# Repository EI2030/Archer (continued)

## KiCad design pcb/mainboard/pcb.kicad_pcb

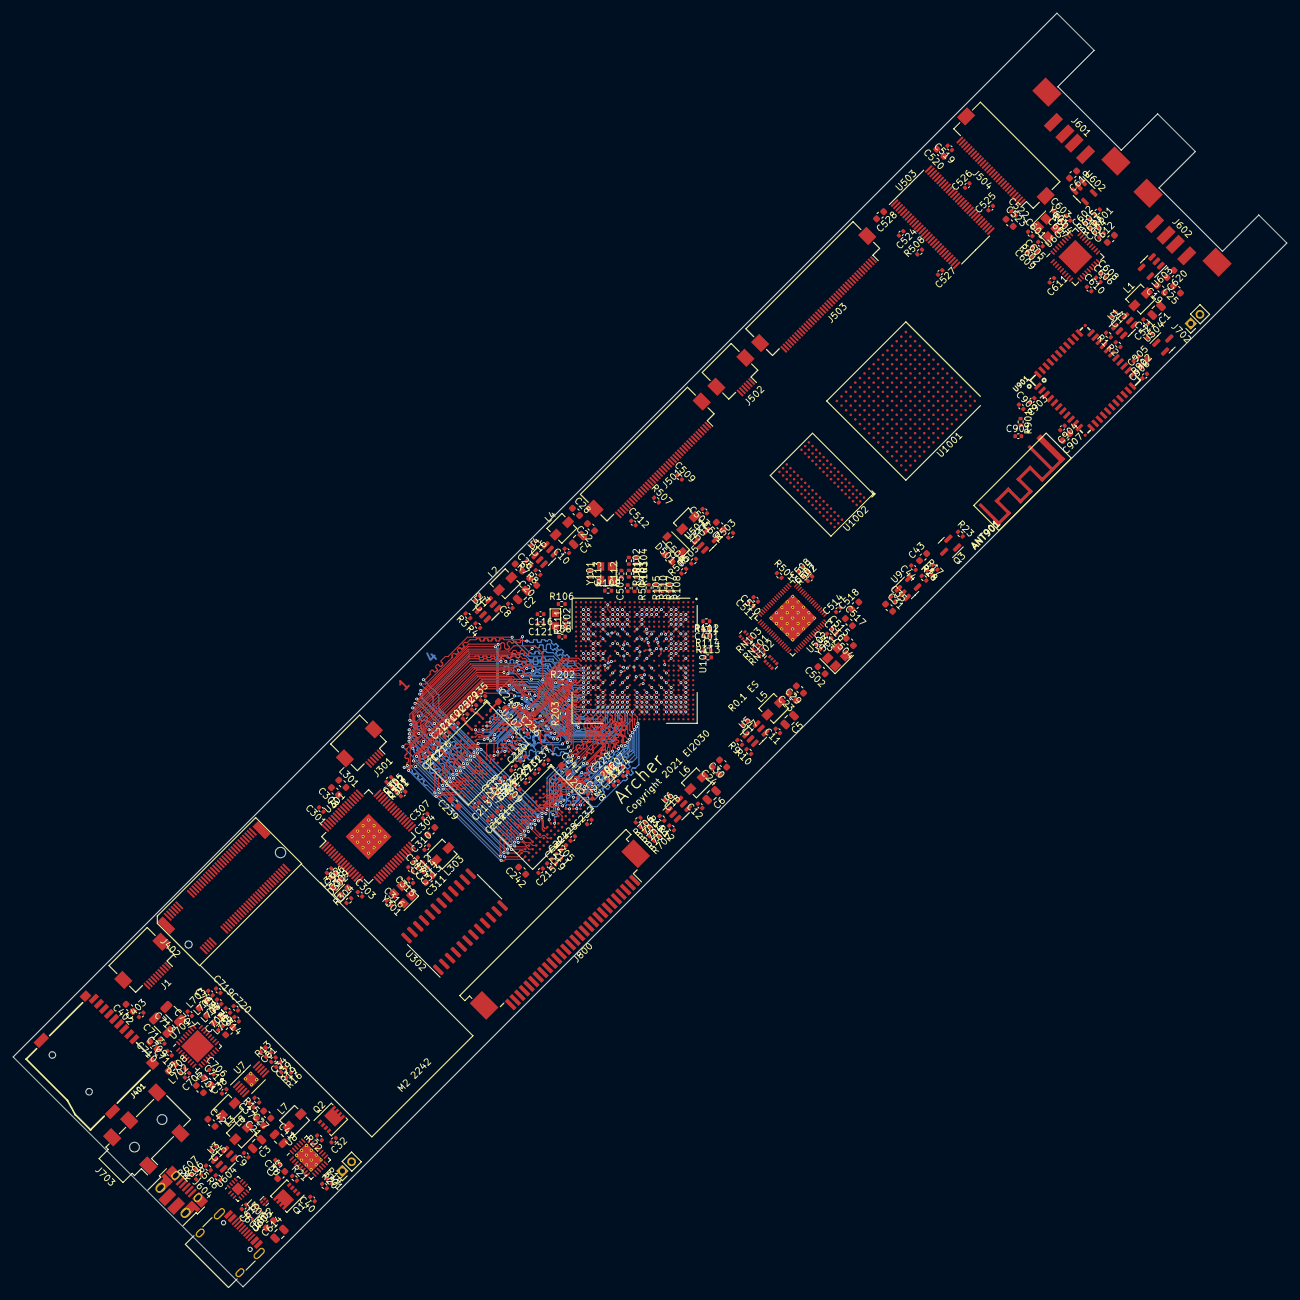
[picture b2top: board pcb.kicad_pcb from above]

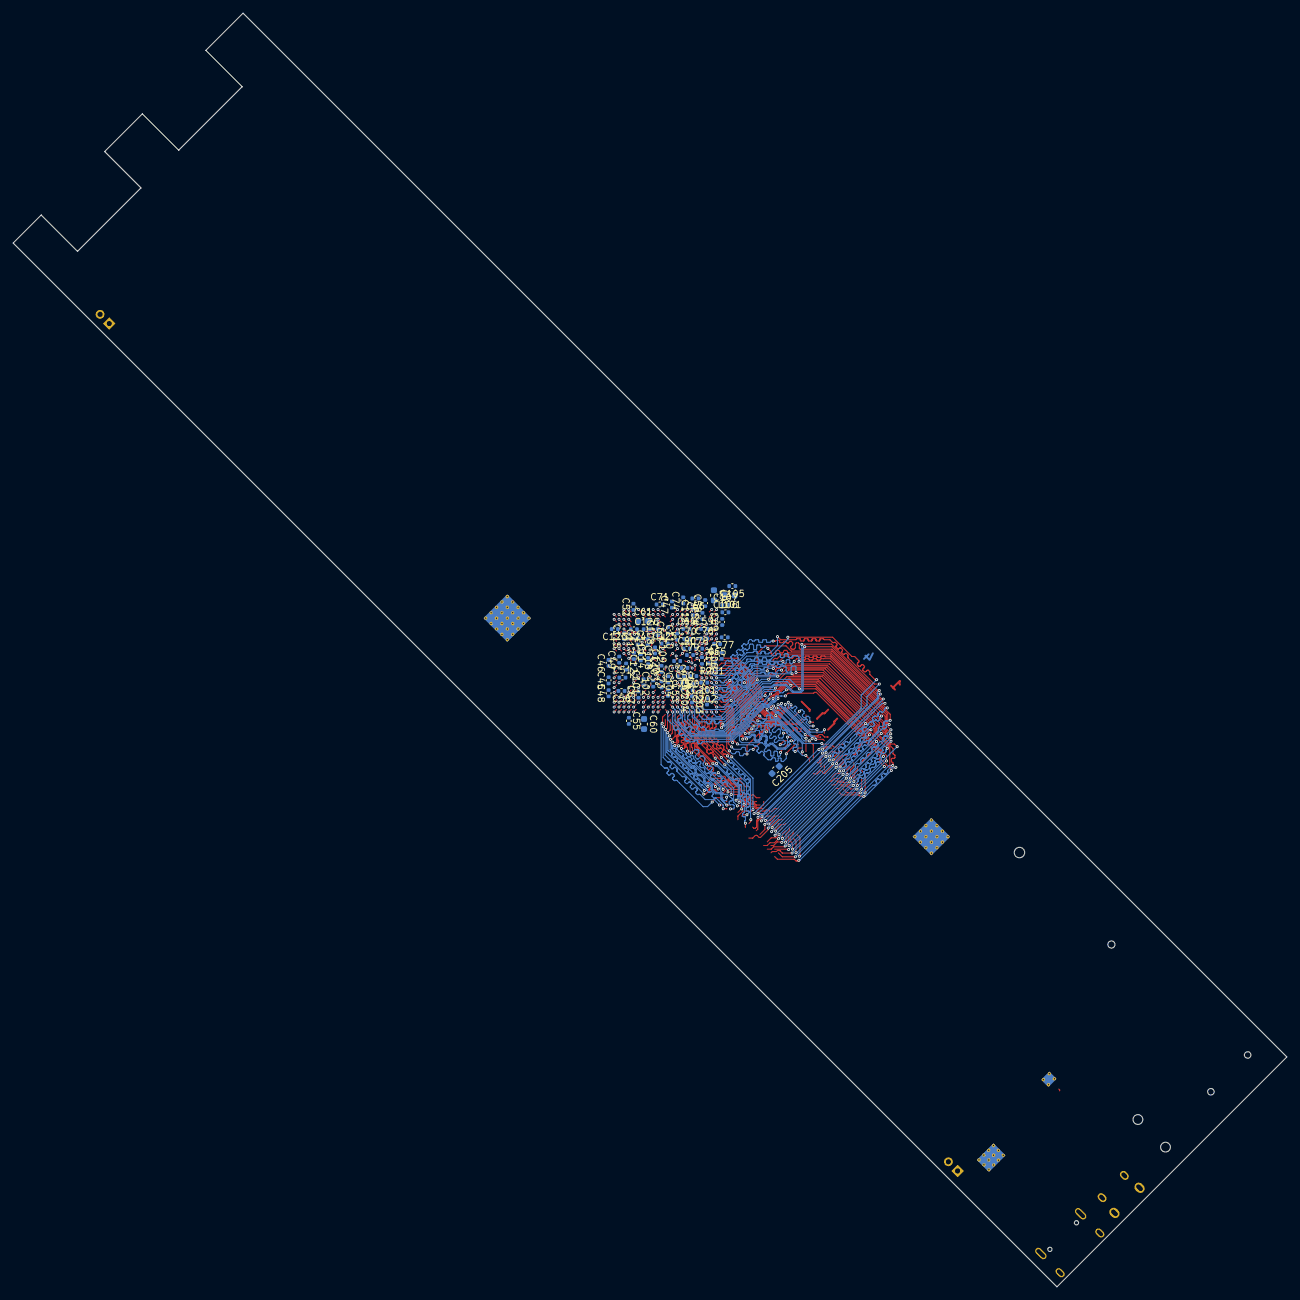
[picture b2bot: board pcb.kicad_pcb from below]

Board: 4 copper layers, 195.9 x 195.9 mm, 388 parts (68 on the bottom side), 385 nets.

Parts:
ANT901: PCB_WIFI_ANT; bt_antenna_1ant_2gnd
C1, C2, C3, C4, C5, C6: 4.7uF/25V; C_0805_2012Metric
C7, C8, C9, C10, C11, C12, C13, C14, C15, C16, C17, C18, C35, C37, C38, C40, C44, C206, C233, C234, C301, C302, C303, C305, C306, C307, C313, C317, C403, C503, C509, C512, C519, C521, C522, C602, C604, C605, C606, C607, C608, C609, C610, C611, C613, C714, C715, C716, C717, C718, C904, C906: 100nF; C_0402_1005Metric
C19, C20, C21, C22, C23, C24, C25, C26, C27, C28, C29, C30, C31, C42, C308, C501, C905, C907: 10uF; C_0603_1608Metric
C32, C81: 1uF; C_0402_1005Metric
C33, C43, C220, C710, C711: 4.7uF; C_0603_1608Metric
C34: 10nF; C_0402_1005Metric
C36: 22nF; C_0402_1005Metric
C39: 10pF; C_0402_1005Metric
C41, C614: 10uF/25V; C_0805_2012Metric
C45, C46, C47, C48, C49, C50, C51, C52, C53, C54, C55, C56, C57, C59, C62, C63, C64, C65, C66, C67, C71, C72, C73, C74, C75, C76, C78, C79, C101, C102, C103, C105, C106, C108, C109, C111, C114, C115, C117, C118, C122, C123, C124, C125, C201, C202, C203, C204, C207, C208, C209, C210, C211, C212, C213, C214, C215, C216, C217, C218, C219, C221, C222, C223, C224, C225, C226, C227, C228, C229, C230, C231, C232, C235, C236, C237, C238, C505, C507, C508, C510, C511, C513, C514, C515, C516, C524, C525, C526, C527: 220nF; C_0402_1005Metric
C58, C68, C69, C70, C77, C80, C104, C107, C110, C119, C120, C126, C309, C314: 2.2uF; C_0402_1005Metric
C60, C61, C205, C239, C240, C241, C242, C304, C311, C402, C517, C518, C528: 22uF; C_0603_1608Metric
C112, C113, C315, C316, C401, C601, C603: 18pF; C_0402_1005Metric
C116, C121: DNP/18pF; C_0402_1005Metric
C310, C312: 47pF; C_0402_1005Metric
C502, C504: 18pF; C_0603_1608Metric
C506: 1uF/35V; C_0603_1608Metric
C520, C523, C612, C619, C620: 10uF/6.3V; C_0603_1608Metric
C705, C706, C707, C708, C709, C719, C720: 470nF; C_0402_1005Metric
C712, C713: 100uF; C_1206_3216Metric
C901, C902: DNP; C_0402_1005Metric
C903: 33pF/50V/5%; C_0402_1005Metric
D302: LED; LED_0603_1608Metric
D501: MBR0530; D_SOD-123
J1: Conn_01x10_MountingPin; Hirose_FH12-10S-0.5SH_1x10-1MP_P0.50mm_Horizontal
J301, J502: Conn_01x06_MountingPin; Hirose_FH12-6S-0.5SH_1x06-1MP_P0.50mm_Horizontal
J401: MICRO_SD(TFC-WPAPR-08); TFC-WPAPR-08
J402: Bus_M.2_Socket_B; M2_BKEY
J501, J503: Conn_01x40_MountingPin; Hirose_FH12-40S-0.5SH_1x40-1MP_P0.50mm_Horizontal
J504: Conn_01x28_MountingPin; Hirose_FH12-28S-0.5SH_1x28-1MP_P0.50mm_Horizontal
J601, J602: USB_A; Connector_USB_905-562A2021S10100
J603: USB_C_Receptacle_USB2.0; USB_C_Receptacle_HRO_TYPE-C-31-M-12
J604: USB_B_Micro; USB_Micro-B_Amphenol_10103594-0001LF_Horizontal
J701, J702: Conn_01x02; PinHeader_1x02_P2.00mm_Vertical
J703: AudioJack3_SwitchT; Jack_3.5mm_PJ327E_5A
J800: Conn_01x28_MountingPin; TE_2-84953-8_1x28-1MP_P1.0mm_Horizontal
L1, L2, L3, L4, L5, L6, L303: 4.7uH; L_Vishay_IHLP-1212
L7: 6.8uH; L_Vishay_IHLP-1212
L8: 10uH; L_Vishay_IHLP-1212
L9, L101, L301, L302, L602, L701, L702: 120R; L_0603_1608Metric
L501: 22uH; L_Vishay_IHLP-1212
L601: EXC14CE900U; L_CommonModeChoke_Panasonic_EXC14CE
L703, L704, L705, L706: 15uH; L_0603_1608Metric
Q1, Q2: FDMC8327L; Diodes_PowerDI3333-8
Q3: 2SK3018; SOT-23
R1, R16: 200K/1%; R_0402_1005Metric
R2, R6, R8, R10, R12: 27K/1%; R_0402_1005Metric
R3, R15: 20K/1%; R_0402_1005Metric
R4: 10K/1%; R_0402_1005Metric
R5: 121K/1%; R_0402_1005Metric
R7, R9: 22.6K/1%; R_0402_1005Metric
R11: 34.8K/1%; R_0402_1005Metric
R13, R23, R601, R708: 100K; R_0402_1005Metric
R14: 63.4K; R_0402_1005Metric
R17: 560K/1%; R_0402_1005Metric
R18, R106: 100K/1%; R_0402_1005Metric
R19: 649K/1%; R_0402_1005Metric
R20, R101, R104, R105, R107, R108, R110, R113, R202, R203, R301, R302, R501, R502, R503, R505, R508, R604, R902: 10K; R_0402_1005Metric
R21, R22: 0.016R; R_0402_1005Metric
R24: 487K/1%; R_0402_1005Metric
R102, R103: DNP/10K; R_0402_1005Metric
R109: 1M; R_0402_1005Metric
R111: DNP/4.75M; R_0402_1005Metric
R112, R114: 200/1%; R_0402_1005Metric
R115: 4.7K/1%; R_0402_1005Metric
R201, R204, R205: 240R 1%; R_0402_1005Metric
R206, R207: 1.5K/0.5%; R_0402_1005Metric
R304, R506: 1K; R_0402_1005Metric
R401: 33; R_0402_1005Metric
R504: 49.9K/1%; R_0402_1005Metric
R507: 3R; R_0402_1005Metric
R602: 12K/1%; R_0402_1005Metric
R603, R605: DNP; R_0402_1005Metric
R606, R607: 22; R_0402_1005Metric
R703, R704, R705, R706, R707: 22R; R_0402_1005Metric
R901: 0R; R_0402_1005Metric
RN101, RN102, RN103: 10K; R_Array_Convex_4x0402
U1, U2, U3, U4, U5, U6: SY8120; TSOT-23-6
U7: LT8606; MSOP-10-1EP_3x3mm_P0.5mm_EP1.68x1.88mm_ThermalVias
U8: LTC4162-F; QFN-28-1EP_4x5mm_P0.5mm_EP2.65x3.65mm_ThermalVias
U9: ADP123; TSOT-23-5
U101: MCIMX7S5EVM08SC; BGA-541_25x25_19.0x19.0mm
U202, U203: MT41K256M16HA; BGA-96_9.0x13.0mm_Layout2x3x16_P0.8mm
U301: LPC5500_FBD64; LQFP-64-1EP_10x10mm_P0.5mm_EP5x5mm_ThermalVias
U302: 74LS154; SO-24_5.3x15mm_P1.27mm
U501: CAT4139; SOT-23-5
U502: SSD2828; QFN-68-1EP_8x8mm_P0.4mm_EP5.2x5.2mm_ThermalVias
U503: DS90C385A; TSSOP-56_6.1x14mm_P0.5mm
U504: SM351LT; SOT-23
U601: USB2514B_Bi; QFN-36-1EP_6x6mm_P0.5mm_EP3.7x3.7mm
U602, U603: AP2171W; SOT-23-5
U604: FUSB302BMPX; WQFN-14-1EP_2.5x2.5mm_P0.5mm_EP1.45x1.45mm
U605: USBLC6-2P6; SOT-666
U701: WM8960; QFN-32-1EP_5x5mm_P0.5mm_EP3.6x3.6mm
U901: RTL8723BS; RL-SM02BD(RTL8723BS)
U1001: DNP/XC7A15T-FTG256; Xilinx_FTG256
U1002: DNP/MT41K64M16HA; BGA-96_9.0x13.0mm_Layout2x3x16_P0.8mm
Y101: 24MHz; Oscillator_SMD_Abracon_ASE-4Pin_3.2x2.5mm
Y102: 32.768kHz; Crystal_SMD_TXC_9HT11-2Pin_2.0x1.2mm_HandSoldering
Y301: 16MHz; Oscillator_SMD_Abracon_ASE-4Pin_3.2x2.5mm
Y501, Y601: 24MHz; Crystal_SMD_3225-4Pin_3.2x2.5mm

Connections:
+1V0: C22.2, C28.2, C46.1, C47.1, C49.1, C50.1, C52.1, C53.1, C56.1, C57.1, C61.1, C62.1, C71.1, C72.1, C73.1, C74.1, C75.1, L4.2, R7.2, U101.C14 (VDD_SOC_IN), U101.D14 (VDD_SOC_IN), U101.F3 (VDD_SOC_IN), U101.F4 (VDD_SOC_IN), U101.F18 (VDD_SOC_IN), U101.F19 (VDD_SOC_IN), U101.J3 (VDD_SOC_IN), U101.J4 (VDD_SOC_IN), U101.M3 (VDD_SOC_IN), U101.M4 (VDD_SOC_IN), U101.P18 (VDD_SOC_IN), U101.R3 (VDD_SOC_IN), U101.R4 (VDD_SOC_IN), U101.R17 (VDD_SOC_IN), U101.T18 (VDD_SOC_IN), U101.U13 (VDD_SOC_IN), U101.U15 (VDD_SOC_IN), U101.U17 (VDD_SOC_IN), U101.V12 (VDD_SOC_IN), U101.V14 (VDD_SOC_IN), U101.V16 (VDD_SOC_IN), U101.V18 (VDD_SOC_IN)
+1V2: C507.1, C510.1, C513.1, C515.1, C517.1, U502.15 (MVDD), U502.31 (MVDD), U502.60 (MVDD), U502.66 (MVDD)
+1V8: C20.2, C26.2, C59.1, C101.1, C105.1, C109.1, C508.1, C509.1, C511.1, C514.1, C516.1, C518.1, C705.1, J501.18, J501.19, L2.2, L9.1, L101.1, R3.2, U101.K18 (NVCC_LCD), U101.L9 (NVCC_SPI), U101.V8 (FUSE_FSOURCE), U101.W6 (VDD_LPSR_IN), U502.16 (VDDIO), U502.33 (VDDIO), U502.64 (VDDIO), U502.68 (VDDIO), U701.8 (DCVDD)
+1V8A: C54.1, C58.1, C111.1, L9.2, U101.V5 (VDD_XTAL_1P8), U101.V6 (VDDA_1P8), U101.W5 (VDDA_1P8)
+1V35: C24.2, C30.2, C201.1, C202.1, C203.1, C204.1, C205.1, C207.1, C212.1, C213.1, C214.1, C215.1, C216.1, C217.1, C218.1, C219.1, C220.1, C221.1, C222.1, C223.1, C224.1, C225.1, C226.1, C227.1, C228.1, C229.1, C230.1, C231.1, C232.1, C233.1, C235.1, C236.1, C237.1, C238.1, C239.1, C240.1, C241.1, C242.1, L6.2, R11.2, R206.1, U101.AA16 (NVCC_DRAM), U101.AA17 (NVCC_DRAM), U101.AA18 (NVCC_DRAM), U101.AA19 (NVCC_DRAM), U101.AA20 (NVCC_DRAM), U101.AA21 (NVCC_DRAM), U101.T21 (NVCC_DRAM), U101.U21 (NVCC_DRAM), U101.V21 (NVCC_DRAM), U101.W21 (NVCC_DRAM), U101.Y20 (NVCC_DRAM_CKE), U101.Y21 (NVCC_DRAM), U202.A1 (VDDQ), U202.A8 (VDDQ), U202.B2 (VDD), U202.C1 (VDDQ), U202.C9 (VDDQ), U202.D2 (VDDQ), U202.D9 (VDD), U202.E9 (VDDQ), U202.F1 (VDDQ), U202.G7 (VDD), U202.H2 (VDDQ), U202.H9 (VDDQ), U202.K2 (VDD), U202.K8 (VDD), U202.N1 (VDD), U202.N9 (VDD), U202.R1 (VDD), U202.R9 (VDD), U203.A1 (VDDQ), U203.A8 (VDDQ), U203.B2 (VDD), U203.C1 (VDDQ), U203.C9 (VDDQ), U203.D2 (VDDQ), U203.D9 (VDD), U203.E9 (VDDQ), U203.F1 (VDDQ), U203.G7 (VDD), U203.H2 (VDDQ), U203.H9 (VDDQ), U203.K2 (VDD), U203.K8 (VDD), U203.N1 (VDD), U203.N9 (VDD), U203.R1 (VDD), U203.R9 (VDD), U1002.A1 (VDDQ), U1002.A8 (VDDQ), U1002.B2 (VDD), U1002.C1 (VDDQ), U1002.C9 (VDDQ), U1002.D2 (VDDQ), U1002.D9 (VDD), U1002.E9 (VDDQ), U1002.F1 (VDDQ), U1002.G7 (VDD), U1002.H2 (VDDQ), U1002.H9 (VDDQ), U1002.K2 (VDD), U1002.K8 (VDD), U1002.N1 (VDD), U1002.N9 (VDD), U1002.R1 (VDD), U1002.R9 (VDD)
+3V3: C21.2, C27.2, C63.1, C64.1, C102.1, C103.1, C108.1, C114.1, C115.1, C122.1, C124.1, C125.1, C402.1, C403.1, C512.1, C519.1, C520.1, C521.1, C524.1, C525.1, C526.1, C527.1, C528.1, C604.1, C607.1, C608.1, C609.1, C610.1, C611.1, C612.1, C904.1, C905.1, C906.1, C907.1, J401.4 (VDD), J501.38, J501.39, J502.3, J503.39, J503.40, J504.27, J504.28, L3.2, L701.2, L702.2, R5.2, R105.1, R107.1, R108.1, R110.1, R508.1, R601.1, R604.2, R902.1, RN101.5 (R4.2), RN101.6 (R3.2), RN101.7 (R2.2), RN101.8 (R1.2), U101.F9 (VDD_USB_OTG2_3P3_IN), U101.F10 (VDD_USB_OTG1_3P3_IN), U101.F12 (NVCC_SAI), U101.H8 (NVCC_SD2), U101.K8 (NVCC_SD3), U101.L17 (NVCC_EPDC2), U101.M8 (NVCC_I2C), U101.M18 (NVCC_EPDC1), U101.N9 (NVCC_UART), U101.P8 (NVCC_GPIO1), U101.T8 (NVCC_GPIO2), U503.1 (VCC), U503.9 (VCC), U503.26 (VCC), U503.34 (PLL_VCC), U503.44 (LVDS_VCC), U504.1 (VCC), U601.5 (VDDA33), U601.10 (VDDA33), U601.15 (VDD33), U601.23 (VDD33), U601.27 (VBUS_DET), U601.29 (VDDA33), U601.36 (VDDA33), U901.9 (VDD33), U901.22 (VDD_IO)
+3V3_SB: C39.1, C42.2, C301.1, C304.1, C307.1, C310.1, C317.1, C613.1, J301.1, L8.2, L301.1, L302.1, R13.2, R19.1, R101.2, R103.2, R301.1, R302.1, U8.15 (DVCC), U101.AD8 (VDD_SNVS_IN), U301.25 (USB1_VBUS), U301.27 (USB1_3V3), U301.32 (VBAT_DCDC), U301.33 (VBAT_PMU), U301.61 (USB0_3V3), U302.24 (VCC), U604.3 (VDD), U604.4 (VDD), U604.12 (VCONN), U604.13 (VCONN)
+5V: C19.2, C25.2, C31.1, C35.1, C501.2, C503.2, C522.1, C523.1, J503.37, J503.38, J504.1, J504.2, L1.2, L501.1, R1.2, U9.1 (VIN), U9.3 (EN), U501.5 (IN), U602.5 (IN), U603.5 (IN)
+DRAM_VREF: C206.1, C208.1, C209.1, C210.1, C211.1, C233.2, C234.1, R206.2, R207.1, U101.AC13 (DRAM_VREF), U202.H1 (VrefDQ), U202.M8 (VrefCA), U203.H1 (VrefDQ), U203.M8 (VrefCA)
+SYS: C1.2, C2.2, C3.2, C4.2, C5.2, C6.2, C7.2, C8.2, C9.2, C10.2, C11.2, C12.2, C41.2, C81.2, Q2.5 (D), R21.1, U1.5 (VIN), U2.5 (VIN), U3.5 (VIN), U4.5 (VIN), U5.5 (VIN), U6.5 (VIN), U7.9 (VIN), U7.10 (EN/UV), U8.3 (VOUTA), U8.4 (CLN), U8.27 (VOUT), U8.28 (VOUT)
+VCCIO_SD: C43.1, C44.1, R17.1, R24.1, U9.5 (VOUT)
+VCCIO_WL: C123.1, U101.E7 (NVCC_SD1)
/audio/MICBIAS: C715.1, U701.1 (MICBIAS)
/ddr/DRAM_ADDR0: U101.AB19 (DRAM_ADDR0), U202.N3 (A0), U203.N3 (A0)
/ddr/DRAM_ADDR1: U101.AB16 (DRAM_ADDR1), U202.P7 (A1), U203.P7 (A1)
/ddr/DRAM_ADDR2: U101.AC18 (DRAM_ADDR2), U202.P3 (A2), U203.P3 (A2)
/ddr/DRAM_ADDR3: U101.AC20 (DRAM_ADDR3), U202.N2 (A3), U203.N2 (A3)
/ddr/DRAM_ADDR4: U101.AB21 (DRAM_ADDR4), U202.P8 (A4), U203.P8 (A4)
/ddr/DRAM_ADDR5: U101.Y23 (DRAM_ADDR5), U202.P2 (A5), U203.P2 (A5)
/ddr/DRAM_ADDR6: U101.V22 (DRAM_ADDR6), U202.R8 (A6), U203.R8 (A6)
/ddr/DRAM_ADDR7: U101.Y22 (DRAM_ADDR7), U202.R2 (A7), U203.R2 (A7)
/ddr/DRAM_ADDR8: U101.W22 (DRAM_ADDR8), U202.T8 (A8), U203.T8 (A8)
/ddr/DRAM_ADDR9: U101.V23 (DRAM_ADDR9), U202.R3 (A9), U203.R3 (A9)
/ddr/DRAM_ADDR10: U101.T23 (DRAM_ADDR10), U202.L7 (A10), U203.L7 (A10)
/ddr/DRAM_ADDR11: U101.U22 (DRAM_ADDR11), U202.R7 (A11), U203.R7 (A11)
/ddr/DRAM_ADDR12: U101.T22 (DRAM_ADDR12), U202.N7 (A12/~BC), U203.N7 (A12/~BC)
/ddr/DRAM_ADDR13: U101.P23 (DRAM_ADDR13), U202.T3 (A13), U203.T3 (A13)
/ddr/DRAM_ADDR14: U101.AB18 (DRAM_ADDR14), U202.T7 (A14/NC), U203.T7 (A14/NC)
/ddr/DRAM_BA0: U101.R22 (DRAM_SDBA0), U202.M2 (BA0), U203.M2 (BA0)
/ddr/DRAM_BA1: U101.P22 (DRAM_SDBA1), U202.N8 (BA1), U203.N8 (BA1)
/ddr/DRAM_BA2: U101.N23 (DRAM_SDBA2), U202.M3 (BA2), U203.M3 (BA2)
/ddr/DRAM_CASB: U101.AC14 (~DRAM_CAS), U202.K3 (~CAS), U203.K3 (~CAS)
/ddr/DRAM_CKE: R202.2, U101.AB17 (DRAM_SDCKE0), U202.K9 (CKE), U203.K9 (CKE)
/ddr/DRAM_CKN: U101.AD25 (DRAM_SDCLK0_N), U202.K7 (~CK), U203.K7 (~CK)
/ddr/DRAM_CKP: U101.AD24 (DRAM_SDCLK0_P), U202.J7 (CK), U203.J7 (CK)
/ddr/DRAM_CSB: U101.AB23 (~DRAM_CS0), U202.L2 (~CS), U203.L2 (~CS)
/ddr/DRAM_DATA0: U101.AD22 (DRAM_DATA0), U202.A7 (DQ12)
/ddr/DRAM_DATA1: U101.AD23 (DRAM_DATA1), U202.A3 (DQ15)
/ddr/DRAM_DATA2: U101.AE20 (DRAM_DATA2), U202.C2 (DQ11)
/ddr/DRAM_DATA3: U101.AE23 (DRAM_DATA3), U202.A2 (DQ13)
/ddr/DRAM_DATA4: U101.AE22 (DRAM_DATA4), U202.D7 (DQ8)
/ddr/DRAM_DATA5: U101.AD19 (DRAM_DATA5), U202.B8 (DQ14)
/ddr/DRAM_DATA6: U101.AD18 (DRAM_DATA6), U202.C3 (DQ9)
/ddr/DRAM_DATA7: U101.AE19 (DRAM_DATA7), U202.C8 (DQ10)
/ddr/DRAM_DATA8: U101.AE14 (DRAM_DATA8), U202.G2 (DQ6)
/ddr/DRAM_DATA9: U101.AE18 (DRAM_DATA9), U202.E3 (DQ0)
/ddr/DRAM_DATA10: U101.AE17 (DRAM_DATA10), U202.F2 (DQ2)
/ddr/DRAM_DATA11: U101.AD16 (DRAM_DATA11), U202.H3 (DQ4)
/ddr/DRAM_DATA12: U101.AE16 (DRAM_DATA12), U202.H8 (DQ5)
/ddr/DRAM_DATA13: U101.AD14 (DRAM_DATA13), U202.F8 (DQ3)
/ddr/DRAM_DATA14: U101.AD13 (DRAM_DATA14), U202.F7 (DQ1)
/ddr/DRAM_DATA15: U101.AE13 (DRAM_DATA15), U202.H7 (DQ7)
/ddr/DRAM_DATA16: U101.AA25 (DRAM_DATA16), U203.G2 (DQ6)
/ddr/DRAM_DATA17: U101.W24 (DRAM_DATA17), U203.E3 (DQ0)
/ddr/DRAM_DATA18: U101.V25 (DRAM_DATA18), U203.F2 (DQ2)
/ddr/DRAM_DATA19: U101.W25 (DRAM_DATA19), U203.H3 (DQ4)
/ddr/DRAM_DATA20: U101.AC25 (DRAM_DATA20), U203.F8 (DQ3)
/ddr/DRAM_DATA21: U101.AB25 (DRAM_DATA21), U203.F7 (DQ1)
/ddr/DRAM_DATA22: U101.AB24 (DRAM_DATA22), U203.H8 (DQ5)
/ddr/DRAM_DATA23: U101.AC24 (DRAM_DATA23), U203.H7 (DQ7)
/ddr/DRAM_DATA24: U101.R25 (DRAM_DATA24), U203.A2 (DQ13)
/ddr/DRAM_DATA25: U101.N24 (DRAM_DATA25), U203.A7 (DQ12)
/ddr/DRAM_DATA26: U101.P25 (DRAM_DATA26), U203.C2 (DQ11)
/ddr/DRAM_DATA27: U101.N25 (DRAM_DATA27), U203.B8 (DQ14)
/ddr/DRAM_DATA28: U101.U25 (DRAM_DATA28), U203.D7 (DQ8)
/ddr/DRAM_DATA29: U101.R24 (DRAM_DATA29), U203.C8 (DQ10)
/ddr/DRAM_DATA30: U101.U24 (DRAM_DATA30), U203.A3 (DQ15)
/ddr/DRAM_DATA31: U101.V24 (DRAM_DATA31), U203.C3 (DQ9)
/ddr/DRAM_DQM0: U101.AD20 (DRAM_DQM0), U202.D3 (UDM)
/ddr/DRAM_DQM1: U101.AD17 (DRAM_DQM1), U202.E7 (LDM)
/ddr/DRAM_DQM2: U101.AA24 (DRAM_DQM2), U203.E7 (LDM)
/ddr/DRAM_DQM3: U101.P24 (DRAM_DQM3), U203.D3 (UDM)
/ddr/DRAM_ODT: U101.AC16 (DRAM_ODT0), U202.K1 (ODT), U203.K1 (ODT)
/ddr/DRAM_RASB: U101.AB15 (~DRAM_RAS), U202.J3 (~RAS), U203.J3 (~RAS)
/ddr/DRAM_RST: R203.2, U101.AC22 (DRAM_RESET), U202.T2 (~RESET), U203.T2 (~RESET)
/ddr/DRAM_SDQSN_0: U101.AD21 (DRAM_SDQS0_N), U202.B7 (~UDQS)
/ddr/DRAM_SDQSN_1: U101.AE15 (DRAM_SDQS1_N), U202.G3 (~LDQS)
/ddr/DRAM_SDQSN_2: U101.Y25 (DRAM_SDQS2_N), U203.G3 (~LDQS)
/ddr/DRAM_SDQSN_3: U101.T25 (DRAM_SDQS3_N), U203.B7 (~UDQS)
/ddr/DRAM_SDQSP_0: U101.AE21 (DRAM_SDQS0_P), U202.C7 (UDQS)
/ddr/DRAM_SDQSP_1: U101.AD15 (DRAM_SDQS1_P), U202.F3 (LDQS)
/ddr/DRAM_SDQSP_2: U101.Y24 (DRAM_SDQS2_P), U203.F3 (LDQS)
/ddr/DRAM_SDQSP_3: U101.T24 (DRAM_SDQS3_P), U203.C7 (UDQS)
/ddr/DRAM_WEB: U101.AB14 (~DRAM_SDWE), U202.L3 (~WE), U203.L3 (~WE)
/ec/EC_SWCLK: J301.4, U301.6 (PIO0_11)
/ec/EC_SWDIO: J301.5, U301.5 (PIO0_12)
/ec/KSOE: U301.50 (PIO0_22), U302.18 (E0)
/ec/KSOS1: U301.38 (PIO0_18), U302.23 (A0)
/ec/KSOS2: U301.58 (PIO0_19), U302.22 (A1)
/ec/KSOS3: U301.48 (PIO0_20), U302.21 (A2)
/ec/KSOS4: U301.49 (PIO0_21), U302.20 (A3)
/ec/LED: D302.2 (A), U301.13 (PIO0_10)
/lcd/LEDA: C506.2, D501.1 (K), J501.35, J501.36
/lcd/LEDK: J501.28, J501.29, R506.1, R507.1
/lcd/LVDS_CKN: J504.11, U503.40 (TxCLKOUT-)
/lcd/LVDS_CKP: J504.10, U503.39 (TxCLKOUT+)
/lcd/LVDS_D0N: J504.20, U503.48 (TxOUT0-)
/lcd/LVDS_D0P: J504.19, U503.47 (TxOUT0+)
/lcd/LVDS_D1N: J504.17, U503.46 (TxOUT1-)
/lcd/LVDS_D1P: J504.16, U503.45 (TxOUT1+)
/lcd/LVDS_D2N: J504.14, U503.42 (TxOUT2-)
/lcd/LVDS_D2P: J504.13, U503.41 (TxOUT2+)
/lcd/LVDS_D3N: J504.8, U503.38 (TxOUT3-)
/lcd/LVDS_D3P: J504.7, U503.37 (TxOUT3+)
/lcd/MIPI_CN: J501.9, U502.8 (MIPI_CN)
/lcd/MIPI_CP: J501.8, U502.7 (MIPI_CP)
/lcd/MIPI_DN0: J501.3, U502.2 (MIPI_DN0)
/lcd/MIPI_DN1: J501.6, U502.5 (MIPI_DN1)
/lcd/MIPI_DN2: J501.12, U502.11 (MIPI_DN2)
/lcd/MIPI_DN3: J501.15, U502.14 (MIPI_DN3)
/lcd/MIPI_DP0: J501.2, U502.1 (MIPI_DP0)
/lcd/MIPI_DP1: J501.5, U502.4 (MIPI_DP1)
/lcd/MIPI_DP2: J501.11, U502.10 (MIPI_DP2)
/lcd/MIPI_DP3: J501.14, U502.13 (MIPI_DP3)
/power/1V0_ARM: C23.2, C29.2, C45.1, C48.1, C51.1, C55.1, C60.1, L5.2, R9.2, U101.C17 (VDD_ARM_IN), U101.C20 (VDD_ARM_IN), U101.D17 (VDD_ARM_IN), U101.D20 (VDD_ARM_IN), U101.F22 (VDD_ARM_IN), U101.F23 (VDD_ARM_IN), U101.J22 (VDD_ARM_IN), U101.J23 (VDD_ARM_IN)
/power/BAT+: J1.1, J1.2, J1.3, J1.4, R22.1, U8.19 (BATSENS+), U8.20 (CSN)
/power/BAT_NTC: J1.5, R20.1, U8.10 (NTC)
/power/INTVCC: C33.2, U8.2 (INTVCC), U8.18 (CELLS1)
/power/VCC2P5: C32.2, U8.8 (VCC2P5), U8.17 (CELLS0)
/usb/OCI1B: U601.13 (OCS_N1), U602.3 (~FLG)
/usb/OCI2B: U601.17 (OCS_N2), U603.3 (~FLG)
/usb/PPON1: U601.12 (PRTPWR1/BC_EN1), U602.4 (EN)
/usb/PPON2: U601.16 (PRTPWR2/BC_EN2), U603.4 (EN)
/usb/TYPEC_DN: J603.A7 (D-), J603.B7 (D-), L601.4, U605.3 (I/O2), U605.4 (I/O2)
/usb/TYPEC_DP: J603.A6 (D+), J603.B6 (D+), L601.3, U605.1 (I/O1), U605.6 (I/O1)
/usb/USB_DM1: J601.2 (D-), U601.1 (USBDM_DN1/PRT_DIS_M1)
/usb/USB_DM2: J602.2 (D-), U601.3 (USBDM_DN2/PRT_DIS_M2)
/usb/USB_DP1: J601.3 (D+), U601.2 (USBDP_DN1/PRT_DIS_P1)
/usb/USB_DP2: J602.3 (D+), U601.4 (USBDP_DN2/PRT_DIS_P2)
/usb/VBUS1: C619.1, J601.1 (VBUS), U602.1 (OUT)
/usb/VBUS2: C620.1, J602.1 (VBUS), U603.1 (OUT)
AP_WAKE_BT: U101.T1 (GPIO_IO11), U901.6 (BT_WAKE)
ARM_EN: U5.4 (RUN), U301.42 (PIO1_3)
BT_CFG_1: RN101.4 (R4.1), U101.A22 (LCD1_DATA1), U502.36 (DATA1)
BT_CFG_2: RN103.5 (R4.2), U101.B22 (LCD1_DATA2), U502.37 (DATA2)
BT_CFG_3: RN103.6 (R3.2), U101.A23 (LCD1_DATA3), U502.38 (DATA3)
BT_CFG_4: RN101.3 (R3.1), U101.C22 (LCD1_DATA4), U502.39 (DATA4)
BT_CFG_5: RN103.8 (R1.2), U101.B23 (LCD1_DATA5), U502.40 (DATA5)
BT_CFG_6: RN103.7 (R2.2), U101.A24 (LCD1_DATA6), U502.41 (DATA6)
BT_CFG_10: RN102.5 (R4.2), U101.B24 (LCD1_DATA10), U502.45 (DATA10)
BT_CFG_11: RN102.8 (R1.2), U101.G20 (LCD1_DATA11), U502.46 (DATA11)
BT_CFG_12: RN101.2 (R2.1), U101.F21 (LCD1_DATA12), U502.47 (DATA12)
BT_CFG_13: RN102.7 (R2.2), U101.E22 (LCD1_DATA13), U502.48 (DATA13)
BT_CFG_14: RN102.6 (R3.2), U101.D23 (LCD1_DATA14), U502.49 (DATA14)
BT_RST_N: U101.T3 (GPIO_IO13), U901.34 (BT_DIS#)
BT_WAKE_AP: U101.T2 (GPIO_IO12), U901.7 (BT_HOST_WAKE)
CCM_CLKO2: R902.2, U101.C4 (SD1_WP), U901.24 (SUSCLK_IN/GPIO6)
DEBUG_USB_DM: R607.2, U301.63 (USB0_DM)
DEBUG_USB_DP: R606.2, U301.62 (USB0_DP)
EC_I2C_SCL: U8.14 (SDA), U604.6 (SCL)
EC_I2C_SDA: U8.13 (SCL), U604.7 (SDA)
EC_INT: U8.12 (~SMBALERT), U301.39 (PIO1_1)
EC_SCL: R302.2, U301.47 (PIO0_14)
EC_SDA: R301.2, U301.46 (PIO0_13)
EC_USB_DM: U301.24 (USB1_DM), U601.6 (USBDM_DN3/PRT_DIS_M3)
EC_USB_DP: U301.23 (USB1_DP), U601.7 (USBDP_DN3/PRT_DIS_P3)
EPDC_BDR0: J503.27, U101.K24 (EPDC_BDR0), U503.24 (TxIN22)
EPDC_D0: J503.2, U101.P20 (EPDC_D0), U503.51 (TxIN0)
EPDC_D1: J503.3, U101.P21 (EPDC_D1), U503.52 (TxIN1)
EPDC_D2: J503.4, U101.N20 (EPDC_D2), U503.54 (TxIN2)
EPDC_D3: J503.5, U101.N21 (EPDC_D3), U503.55 (TxIN3)
EPDC_D4: J503.6, U101.N22 (EPDC_D4), U503.56 (TxIN4)
EPDC_D5: J503.7, U101.M20 (EPDC_D5), U503.2 (TxIN5)
EPDC_D6: J503.8, U101.M21 (EPDC_D6), U503.3 (TxIN6)
EPDC_D7: J503.9, U101.M22 (EPDC_D7), U503.4 (TxIN7)
EPDC_D8: J503.11, U101.M23 (EPDC_D8), U503.6 (TxIN8)
EPDC_D9: J503.12, U101.L25 (EPDC_D9), U503.7 (TxIN9)
EPDC_D10: J503.13, U101.L24 (EPDC_D10), U503.8 (TxIN10)
EPDC_D11: J503.14, U101.L23 (EPDC_D11), U503.10 (TxIN11)
EPDC_D12: J503.15, U101.L22 (EPDC_D12), U503.11 (TxIN12)
EPDC_D13: J503.16, U101.L21 (EPDC_D13), U503.12 (TxIN13)
EPDC_D14: J503.17, U101.L20 (EPDC_D14), U503.14 (TxIN14)
EPDC_D15: J503.18, U101.K25 (EPDC_D15), U503.15 (TxIN15)
EPDC_GDCLK: J503.24, U101.J25 (EPDC_GDCLK), U503.20 (TxIN19)
EPDC_GDOE: J503.25, U101.J24 (EPDC_GDOE), U503.22 (TxIN20)
EPDC_GDSP: J503.26, U101.H25 (EPDC_GDSP), U503.23 (TxIN21)
EPDC_PWRSTAT: J503.32, J504.5, U101.K20 (EPDC_PWRSTAT)
EPDC_SDCE0: J503.20, U101.G25 (EPDC_SDCE0), U503.16 (TxIN16)
EPDC_SDCLK: J503.29, U101.J21 (EPDC_SDCLK), U503.31 (TxCLKIN)
EPDC_SDLE: J503.21, U101.J20 (EPDC_SDLE), U503.18 (TxIN17)
EPDC_SDOE: J503.22, U101.H21 (EPDC_SDOE), U503.19 (TxIN18)
EPD_PWR_EN: J503.31, J504.4, U503.32 (~PWR_DWN)
EPD_TP_INT: J503.33, J504.25
GND: ANT901.2, C1.1, C2.1, C3.1, C4.1, C5.1, C6.1, C7.1, C8.1, C9.1, C10.1, C11.1, C12.1, C19.1, C20.1, C21.1, C22.1, C23.1, C24.1, C25.1, C26.1, C27.1, C28.1, C29.1, C30.1, C31.2, C32.1, C33.1, C34.1, C35.2, C37.1, C40.1, C41.1, C42.1, C43.2, C44.2, C45.2, C46.2, C47.2, C48.2, C49.2, C50.2, C51.2, C52.2, C53.2, C54.2, C55.2, C56.2, C57.2, C58.2, C59.2, C60.2, C61.2, C62.2, C63.2, C64.2, C65.1, C66.1, C67.1, C68.1, C69.1, C70.1, C71.2, C72.2, C73.2, C74.2, C75.2, C76.1, C77.1, C78.1, C79.1, C80.1, C81.1, C101.2, C102.2, C103.2, C104.2, C105.2, C106.2, C107.2, C108.2, C109.2, C110.2, C111.2, C112.2, C113.2, C114.2, C115.2, C116.2, C117.2, C118.2, C119.2, C120.2, C121.2, C122.2, C123.2, C124.2, C125.2, C126.2, C201.2, C202.2, C203.2, C204.2, C205.2, C206.2, C207.2, C208.2, C209.2, C210.2, C211.2, C212.2, C213.2, C214.2, C215.2, C216.2, C217.2, C218.2, C219.2, C220.2, C221.2, C222.2, C223.2, C224.2, C225.2, C226.2, C227.2, C228.2, C229.2, C230.2, C231.2, C232.2, C234.2, C235.2, C236.2, C237.2, C238.2, C239.2, C240.2, C241.2, C242.2, C301.2, C302.2, C303.2, C304.2, C305.2, C306.2, C307.2, C308.2, C309.2, C310.2, C311.2, C312.2, C313.2, C314.2, C315.2, C316.2, C317.2, C401.2, C402.2, C403.2, C501.1, C502.1, C503.1, C504.1, C505.1, C506.1, C507.2, C508.2, C509.2, C510.2, C511.2, C512.2, C513.2, C514.2, C515.2, C516.2, C517.2, C518.2, C519.2, C520.2, C521.2, C522.2, C523.2, C524.2, C525.2, C526.2, C527.2, C528.2, C601.1, C602.2, C603.1, C604.2, C605.2, C606.2, C607.2, C608.2, C609.2, C610.2, C611.2, C612.2, C613.2, C614.2, C619.2, C620.2, C705.2, C706.2, C707.2, C708.2, C709.2, C710.2, C711.2, C714.1, C715.2, C716.1, C717.1, C718.1, C901.1, C902.1, C904.2, C905.2, C906.2, C907.2, J1.6, J1.7, J1.8, J1.9, J1.10, J1.MP (MountPin), J301.6, J301.MP (MountPin), J401.6 (VSS), J401.10, J401.11, J401.12, J401.13, J501.1, J501.4, J501.7, J501.10, J501.13, J501.16, J501.17, J501.27, J501.30, J501.32, J501.33, J501.37, J501.MP (MountPin), J502.6, J502.MP (MountPin), J503.1, J503.10, J503.19, J503.23, J503.28, J503.30, J503.36, J503.MP (MountPin), J504.3, J504.6, J504.9, J504.12, J504.15, J504.18, J504.21, J504.24, J504.26, J504.MP (MountPin), J601.4 (GND), J601.5 (Shield), J602.4 (GND), J602.5 (Shield), J603.A1 (GND), J603.A12 (GND), J603.B1 (GND), J603.B12 (GND), J603.S1 (SHIELD), J604.4 (ID), J604.5 (GND), J604.6 (Shield), J703.S, J800.1, J800.MP (MountPin), R2.1, R4.1, R6.1, R8.1, R10.1, R12.1, R14.2, R15.1, R16.1, R18.2, R23.2, R102.1, R104.1, R106.1, R112.2, R113.2, R114.2, R115.1, R201.1, R202.1, R203.1, R204.2, R205.2, R207.2, R304.2, R501.1, R502.1, R503.2, R507.2, R602.2, R603.2, R605.2, RN102.1 (R1.1), RN102.2 (R2.1), RN102.3 (R3.1), RN102.4 (R4.1), RN103.1 (R1.1), RN103.2 (R2.1), RN103.3 (R3.1), RN103.4 (R4.1), U1.2 (GND), U2.2 (GND), U3.2 (GND), U4.2 (GND), U5.2 (GND), U6.2 (GND), U7.11 (GND), U8.16 (SYNC), U8.23 (PGND), U8.24 (PGND), U8.29 (AGND), U9.2 (GND), U101.A1 (GND), U101.A3 (GND), U101.A6 (GND), U101.A9 (GND), U101.A13 (GND), U101.A17 (GND), U101.A21 (GND), U101.A25 (GND), U101.AA1 (GND), U101.AA2 (GND), U101.AA6 (GND), U101.AA8 (GND), U101.AA15 (GND), U101.AA23 (GND), U101.AB1 (ADC2_IN2), U101.AB2 (ADC2_IN3), U101.AB4 (GND), U101.AB5 (GND), U101.AB7 (GND), U101.AB9 (GND), U101.AB12 (GND), U101.AC1 (ADC2_IN0), U101.AC2 (ADC2_IN1), U101.AC6 (GND), U101.AC9 (GND), U101.AC12 (GND), U101.AC15 (GND), U101.AC17 (GND), U101.AC19 (GND), U101.AC21 (GND), U101.AC23 (GND), U101.AD1 (ADC1_IN0), U101.AD2 (GND), U101.AD3 (ADC1_IN1), U101.AD5 (GND), U101.AD7 (GND), U101.AD9 (GND), U101.AD12 (GND), U101.AE1 (GND), U101.AE2 (ADC1_IN2), U101.AE3 (ADC1_IN3), U101.AE5 (GND), U101.AE7 (GND), U101.AE9 (GND), U101.AE12 (GND), U101.AE24 (GND), U101.AE25 (GND), U101.B3 (GND), U101.B6 (GND), U101.B9 (GND), U101.B13 (GND), U101.B17 (GND), U101.B21 (GND), U101.C9 (GND), U101.C13 (GND), U101.C15 (GND), U101.C16 (GND), U101.C18 (GND), U101.C19 (GND), U101.D1 (GND), U101.D2 (GND), U101.D4 (GND), U101.D7 (GND), U101.D10 (GND), U101.D22 (GND), U101.F7 (GND), U101.F8 (GND), U101.F11 (GND), U101.F13 (GND), U101.G4 (GND), U101.G7 (GND), U101.G9 (GND), U101.G11 (GND), U101.G13 (GND), U101.G15 (GND), U101.G17 (GND), U101.G19 (GND), U101.G22 (GND), U101.H1 (GND), U101.H2 (GND), U101.H12 (USB_VDD_H_1P2), U101.H16 (NVCC_ENET1), U101.J7 (GND), U101.J19 (GND), U101.K4 (GND), U101.K10 (GND), U101.K12 (GND), U101.K14 (GND), U101.K16 (GND), U101.K22 (GND), U101.L7 (GND), U101.L11 (GND), U101.L13 (GND), U101.L15 (GND), U101.L19 (GND), U101.M10 (GND), U101.M12 (GND), U101.M14 (GND), U101.M16 (GND), U101.M24 (GND), U101.M25 (GND), U101.N4 (GND), U101.N7 (GND), U101.N11 (GND), U101.N13 (GND), U101.N15 (GND), U101.N19 (GND), U101.P6 (TEST_MODE), U101.P10 (GND), U101.P12 (GND), U101.P14 (GND), U101.P16 (GND), U101.R7 (GND), U101.R11 (GND), U101.R13 (GND), U101.R15 (GND), U101.R19 (GND), U101.R20 (GND), U101.R21 (GND), U101.R23 (GND), U101.T4 (GND), U101.T10 (GND), U101.T12 (GND), U101.T14 (GND), U101.T16 (GND), U101.T20 (GND), U101.U1 (JTAG_MOD), U101.U7 (GND), U101.U11 (GND), U101.U19 (GND), U101.U20 (GND), U101.U23 (GND), U101.V20 (GND), U101.W1 (GND), U101.W2 (GND), U101.W3 (CCM_CLK2), U101.W4 (GND), U101.W7 (GND), U101.W9 (GND), U101.W11 (GND), U101.W13 (GND), U101.W15 (GND), U101.W17 (GND), U101.W19 (GND), U101.W20 (GND), U101.W23 (GND), U101.Y6 (GND), U101.Y13 (GND), U101.Y14 (GND), U101.Y15 (GND), U101.Y16 (GND), U101.Y17 (GND), U101.Y18 (GND), U101.Y19 (GND), U202.A9 (VSS), U202.B1 (VSSQ), U202.B3 (VSS), U202.B9 (VSSQ), U202.D1 (VSSQ), U202.D8 (VSSQ), U202.E1 (VSS), U202.E2 (VSSQ), U202.E8 (VSSQ), U202.F9 (VSSQ), U202.G1 (VSSQ), U202.G8 (VSS), U202.G9 (VSSQ), U202.J2 (VSS), U202.J8 (VSS), U202.M1 (VSS), U202.M9 (VSS), U202.P1 (VSS), U202.P9 (VSS), U202.T1 (VSS), U202.T9 (VSS), U203.A9 (VSS), U203.B1 (VSSQ), U203.B3 (VSS), U203.B9 (VSSQ), U203.D1 (VSSQ), U203.D8 (VSSQ), U203.E1 (VSS), U203.E2 (VSSQ), U203.E8 (VSSQ), U203.F9 (VSSQ), U203.G1 (VSSQ), U203.G8 (VSS), U203.G9 (VSSQ), U203.J2 (VSS), U203.J8 (VSS), U203.M1 (VSS), U203.M9 (VSS), U203.P1 (VSS), U203.P9 (VSS), U203.T1 (VSS), U203.T9 (VSS), U301.11 (VSSA), U301.22 (USB1_VSS), U301.26 (USB1_VSS), U301.30 (VSS_DCDC), U301.64 (USB0_VSS), U301.65 (EP), U501.2 (GND), U502.3 (GND), U502.6 (GND), U502.9 (GND), U502.12 (GND), U502.27 (SHUT), U502.32 (GND), U502.65 (GND), U502.67 (GND), U502.69 (EP), U503.5 (GND), U503.13 (GND), U503.21 (GND), U503.25 (TxIN23), U503.27 (TxIN24), U503.28 (TxIN25), U503.29 (GND), U503.30 (TxIN26), U503.33 (PLL_GND), U503.35 (PLL_GND), U503.36 (LVDS_GND), U503.43 (LVDS_GND), U503.49 (LVDS_GND), U503.50 (TxIN27), U503.53 (GND)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
I2C1_SCL: J502.1, R107.2, U101.J2 (I2C1_SCL), U701.17 (SCLK)
I2C1_SDA: J502.2, R105.2, U101.K1 (I2C1_SDA), U701.18 (SDIN)
I2C2_SCL: J503.35, J504.23, R110.2, U101.K2 (I2C2_SCL)
I2C2_SDA: J503.34, J504.22, R108.2, U101.K3 (I2C2_SDA)
KSI0: J800.27, U301.36 (PIO0_0)
KSI1: J800.24, U301.2 (PIO0_1)
KSI2: J800.22, U301.52 (PIO0_2)
KSI3: J800.20, U301.53 (PIO0_3)
KSI4: J800.18, U301.55 (PIO0_4)
KSI5: J800.17, U301.56 (PIO0_5)
KSI6: J800.15, U301.57 (PIO0_6)
KSI7: J800.14, U301.1 (PIO0_7)
KSO0: J800.28, U302.1 (S0)
KSO1: J800.7, J800.26, U302.2 (S1)
KSO2: J800.25, U302.3 (S2)
KSO3: J800.4, J800.23, U302.4 (S3)
KSO4: J800.21, U302.5 (S4)
KSO5: J800.19, U302.6 (S5)
KSO6: J800.16, U302.7 (S6)
KSO7: J800.13, U302.8 (S7)
KSO8: J800.12, U302.9 (S8)
KSO9: J800.11, U302.10 (S9)
KSO10: J800.10, U302.11 (S10)
KSO11: J800.9, U302.13 (S11)
KSO12: J800.8, U302.14 (S12)
KSO13: J800.6, U302.15 (S13)
KSO14: J800.5, U302.16 (S14)
KSO15: J800.3, U302.17 (S15)
LCD1_CLK: U101.E20 (LCD1_CLK), U502.30 (PCLK)
LCD1_DE: U101.F25 (LCD1_ENABLE), U502.28 (DEN)
LCD1_HSYNC: U101.E25 (LCD1_HSYNC), U502.29 (HSYNC)
LCD1_RESET: J501.24, J502.4, U101.C21 (LCD1_RESET), U502.22 (RESET)
LCD1_VSYNC: U101.F24 (LCD1_VSYNC), U502.34 (VSYNC)
LCD_D0: U101.D21 (LCD1_DATA0), U502.35 (DATA0)
LCD_D7: U101.F20 (LCD1_DATA7), U502.42 (DATA7)
LCD_D8: U101.E21 (LCD1_DATA8), U502.43 (DATA8)
LCD_D9: U101.C23 (LCD1_DATA9), U502.44 (DATA9)
LCD_D15: U101.C24 (LCD1_DATA15), U502.50 (DATA15)
LCD_D16: U101.B25 (LCD1_DATA16), U502.51 (DATA16)
LCD_D17: U101.G21 (LCD1_DATA17), U502.52 (DATA17)
LCD_D18: U101.E23 (LCD1_DATA18), U502.53 (DATA18)
LCD_D19: U101.D24 (LCD1_DATA19), U502.54 (DATA19)
LCD_D20: U101.C25 (LCD1_DATA20), U502.55 (DATA20)
LCD_D21: U101.E24 (LCD1_DATA21), U502.56 (DATA21)
LCD_D22: U101.D25 (LCD1_DATA22), U502.57 (DATA22)
LCD_D23: U101.G23 (LCD1_DATA23), U502.58 (DATA23)
LCD_EN: R503.1, U301.44 (PIO0_28), U501.4 (~SHDN~)
LCD_PWM: R504.2, U101.N2 (GPIO1_IO1)
MPU_RST: U101.R6 (~POR), U301.14 (PIO0_15)
unnamed: ANT901.1, C901.2, R901.2
unnamed: C13.1, L1.1, U1.6 (SW)
unnamed: C13.2, U1.1 (BS)
unnamed: C14.1, L2.1, U2.6 (SW)
unnamed: C14.2, U2.1 (BS)
unnamed: C15.1, L3.1, U3.6 (SW)
unnamed: C15.2, U3.1 (BS)
unnamed: C16.1, L4.1, U4.6 (SW)
unnamed: C16.2, U4.1 (BS)
unnamed: C17.1, L5.1, U5.6 (SW)
unnamed: C17.2, U5.1 (BS)
unnamed: C18.1, L6.1, U6.6 (SW)
unnamed: C18.2, U6.1 (BS)
unnamed: C34.2, U7.7 (TR/SS)
unnamed: C36.1, U8.1 (BOOST)
unnamed: C36.2, L7.1, U8.25 (SW), U8.26 (SW)
unnamed: C37.2, U7.3 (INTVcc)
unnamed: C38.1, L8.1, U7.2 (SW)
unnamed: C38.2, U7.1 (BST)
unnamed: C39.2, R16.2, R19.2, U7.6 (FB)
unnamed: C65.2, C76.2, C77.2, U101.AA9 (VDDD_1P0_CAP), U101.AA10 (PCIE_VP), U101.AA11 (PCIE_VP_TX), U101.AA12 (PCIE_VP_RX), U101.J15 (VDD_MIPI_1P0), U101.J17 (VDD_MIPI_1P0)
unnamed: C66.2, U101.V3 (VDDA_1P0_CAP)
unnamed: C67.2, U101.H18 (MIPI_VREG_0P4V)
unnamed: C68.2, U101.AE8 (VDD_SNVS_1P8_CAP)
unnamed: C69.2, U101.AC5 (VDD_LPSR_1P0_CAP)
unnamed: C70.2, U101.V10 (PVCC_GPIO_CAP)
unnamed: C104.1, U101.N17 (PVCC_EPDC_LCD_CAP)
unnamed: C106.1, C107.1, L101.2, U101.AB3 (VDDA_ADC2_1P8), U101.AC3 (VDDA_ADC1_1P8), U101.AC4 (VDD_TEMPSENSOR_1P8)
unnamed: C110.1, U101.R9 (PVCC_I2C_SPI_UART_CAP)
unnamed: C112.1, R109.2, U101.V2 (XTALO), Y101.1
unnamed: C113.1, R109.1, U101.V1 (XTALI), Y101.3
unnamed: C116.1, R111.2, U101.AD6 (RTC_XTALO), Y102.1
unnamed: C117.1, C119.1, U101.H10 (VDD_USB_OTG1_1P0_CAP)
unnamed: C118.1, C120.1, U101.J11 (VDD_USB_OTG2_1P0_CAP)
unnamed: C121.1, R111.1, U101.AE6 (RTC_XTALI), Y102.2
unnamed: C126.1, U101.J9 (PVCC_SAI_SD_CAP)
unnamed: C302.1, C303.1, C305.1, C308.1, L301.2, U301.8 (VDD), U301.16 (VDD), U301.43 (VDD), U301.54 (VDD)
unnamed: C306.1, C309.1, L302.2, U301.9 (VDDA), U301.10 (VREFP)
unnamed: C311.1, C312.1, C313.1, C314.1, L303.2, U301.28 (VDD_PMU), U301.29 (FB)
unnamed: C315.1, U301.20 (XTAL32M_N), Y301.1
unnamed: C316.1, U301.19 (XTAL32M_P), Y301.3
unnamed: C401.1, J401.5 (CLK/SCLK), R401.1
unnamed: C502.2, U502.62 (TX_CLK_XIO), Y501.1
unnamed: C504.2, U502.63 (TX_CLK_XIN), Y501.3
unnamed: C505.2, R504.1, R505.2
unnamed: C601.2, U601.33 (XTALIN/CLKIN), Y601.1
unnamed: C602.1, R601.2, U601.26 (RESET_N)
unnamed: C603.2, U601.32 (XTALOUT), Y601.3
unnamed: C605.1, U601.34 (PLLFILT)
unnamed: C606.1, U601.14 (CRFILT)
unnamed: C706.1, C707.1, C708.1, C711.1, L701.1, U701.10 (DBVDD), U701.21 (SPKVDD), U701.26 (SPKVDD)
unnamed: C709.1, C710.1, L702.1, U701.32 (AVDD)
unnamed: C712.1, U701.31 (HP_L)
unnamed: C712.2, J703.T
unnamed: C713.1, U701.29 (HP_R)
unnamed: C713.2, J703.R
unnamed: C714.2, C720.2, J702.2, L706.2
unnamed: C716.2, C720.1, J702.1, L705.2
unnamed: C717.2, C719.2, J701.2, L704.2
unnamed: C718.2, C719.1, J701.1, L703.2
unnamed: C902.2, C903.2, R901.1
unnamed: C903.1, U901.2 (WIFI/BT_ANT)
unnamed: D302.1 (K), R304.1
unnamed: D501.2 (A), L501.2, U501.1 (SW)
unnamed: J402.2 (3.3V), J402.4 (3.3V), J402.70 (3.3V), J402.72 (3.3V), J402.74 (3.3V)
unnamed: J402.3 (GND), J402.5 (GND), J402.11 (GND), J402.27 (GND), J402.33 (GND), J402.39 (GND), J402.45 (GND), J402.51 (GND), J402.57 (GND), J402.71 (GND), J402.73 (GND)
unnamed: J603.A5 (CC1), U604.10 (CC1), U604.11 (CC1)
unnamed: J603.B5 (CC2), U604.1 (CC2), U604.14 (CC2)
unnamed: J604.2 (D-), R607.1
unnamed: J604.3 (D+), R606.1
unnamed: J703.TN, R708.2, U701.7 (RINPUT3)
unnamed: L7.2, Q2.1 (S), Q2.2 (S), Q2.3 (S), R22.2, U8.21 (CSP)
unnamed: L303.1, U301.31 (LX)
unnamed: L703.1, U701.25 (SPK_LP)
unnamed: L704.1, U701.23 (SPK_LN)
unnamed: L705.1, U701.22 (SPK_RP)
unnamed: L706.1, U701.19 (SPK_RN)
unnamed: Q1.4 (G), U8.6 (INFET)
unnamed: Q1.5 (D), R21.2, U8.5 (CLP)
unnamed: Q2.4 (G), U8.22 (BATFET)
unnamed: Q3.1 (S), R17.2, R18.1, U9.4 (SENSE/ADJ)
unnamed: Q3.3 (D), R24.2
unnamed: R1.1, R2.2, U1.3 (FB)
unnamed: R3.1, R4.2, U2.3 (FB)
unnamed: R5.1, R6.2, U3.3 (FB)
unnamed: R7.1, R8.2, U4.3 (FB)
unnamed: R9.1, R10.2, U5.3 (FB)
unnamed: R11.1, R12.2, U6.3 (FB)
unnamed: R14.1, U8.11 (RT)
unnamed: R15.2, U7.4 (RT)
unnamed: R20.2, U8.9 (NTCBIAS)
unnamed: R101.1, R102.2, U101.P5 (BOOT_MODE1)
unnamed: R103.1, R104.2, U101.P4 (BOOT_MODE0)
unnamed: R106.2, U101.AE4 (TEMPSENSOR_REXT)
unnamed: R112.1, U101.A7 (USB1_OTG1_REXT)
unnamed: R113.1, U101.B11 (USB_OTG2_ID)
unnamed: R114.1, U101.A11 (USB_OTG2_REXT)
unnamed: R115.2, U101.AA13 (PCIE_REXT)
unnamed: R201.2, U101.AB13 (DRAM_ZQPAD)
unnamed: R204.1, U202.L8 (ZQ)
unnamed: R205.1, U203.L8 (ZQ)
unnamed: R501.2, U502.18 (PS1)
unnamed: R502.2, U502.17 (PS0)
unnamed: R505.1, R506.2, U501.3 (FB)
unnamed: R508.2, U503.17 (R_FB)
unnamed: R602.1, U601.35 (RBIAS)
unnamed: R603.1, U601.24 (SCL/SMBCLK/CFG_SEL0)
unnamed: R604.1, U601.28 (SUSP_IND/LOCAL_PWR/NON_REM0)
unnamed: R605.1, U601.25 (HS_IND/CFG_SEL1)
unnamed: R703.2, U701.13 (DACLRC), U701.15 (ADCLRC)
unnamed: R704.2, U701.12 (BCLK)
unnamed: R705.2, U701.16 (ADCDAT)
unnamed: R706.2, U701.14 (DACDAT)
unnamed: R707.2, U701.11 (MCLK)
unnamed: C78.2, C79.2, C80.2, U101.J13 (VDDA_MIPI_1P8), U101.Y9 (VDDA_PHY_1P8), U101.Y10 (PCIE_VPH), U101.Y11 (PCIE_VPH_TX), U101.Y12 (PCIE_VPH_RX)
unnamed: U302.12 (GND), U302.19 (E1)
PMIC_ON_REQ: U101.AB8 (SNVS_PMIC_ON_REQ), U301.37 (PIO0_9)
PMIC_STBY_REQ: U101.AC7 (PMIC_STBY_REQ), U301.17 (PIO0_8)
PWR_EN: U2.4 (RUN), U3.4 (RUN), U4.4 (RUN), U6.4 (RUN), U301.41 (PIO1_2)
SAI1_MCLK: R707.1, U101.E10 (SAI1_MCLK)
SAI1_RXD: R705.1, U101.E12 (SAI1_RXD)
SAI1_TXC: R704.1, U101.C11 (SAI1_TXC)
SAI1_TXD: R706.1, U101.E11 (SAI1_TXD)
SAI1_TXFS: R703.1, U101.D11 (SAI1_TXFS)
SB_PG: R13.1, U7.8 (PG), U301.21 (~RESET)
SD1_CLK: R401.2, U101.B5 (SD1_CLK)
SD1_CMD: J401.3 (CMD/DI), U101.C5 (SD1_CMD)
SD1_DATA0: J401.7 (DAT0/DO), U101.A5 (SD1_DATA0)
SD1_DATA1: J401.8 (DAT1/RES), U101.D6 (SD1_DATA1)
SD1_DATA2: J401.1 (DAT2/RES), U101.A4 (SD1_DATA2)
SD1_DATA3: J401.2 (CD/DAT3/CS), U101.D5 (SD1_DATA3)
SD1_VSELECT: Q3.2 (G), R23.1, U101.R1 (GPIO1_IO8)
SD2_CLK: U101.E3 (SD2_CLK), U901.17 (SD_CLK)
SD2_CMD: U101.F6 (SD2_CMD), U901.16 (SD_CMD)
SD2_DATA0: U101.E4 (SD2_DATA0), U901.18 (SD_D0)
SD2_DATA1: U101.E5 (SD2_DATA1), U901.19 (SD_D1)
SD2_DATA2: U101.F5 (SD2_DATA2), U901.14 (SD_D2)
SD2_DATA3: U101.E6 (SD2_DATA3), U901.15 (SD_D3)
UART1_RXD: U101.L3 (UART1_RXD), U301.60 (PIO0_30)
UART1_TXD: U101.L4 (UART1_TXD), U301.59 (PIO0_29)
UART3_RTS: U101.M5 (UART3_RTS), U901.44 (UART_CTS)
UART3_RXD: U101.M1 (UART3_RXD), U901.42 (UART_OUT)
UART3_TXD: U101.M2 (UART3_TXD), U901.43 (UART_IN)
USB_HOST_DN: U101.A10 (USB_OTG2_DN), U601.30 (USBDM_UP)
USB_HOST_DP: U101.B10 (USB_OTG2_DP), U601.31 (USBDP_UP)
USB_OTG_DN: L601.1, U101.A8 (USB_OTG1_DN)
USB_OTG_DP: L601.2, U101.B8 (USB_OTG1_DP)
USB_OTG_ID: U101.B7 (USB_OTG1_ID), U301.4 (PIO1_0)
VBUS: C40.2, C614.1, L602.1, Q1.1 (S), Q1.2 (S), Q1.3 (S), U8.7 (VIN)
VBUS_IN: J603.A4 (VBUS), J603.A9 (VBUS), J603.B4 (VBUS), J603.B9 (VBUS), L602.2, U604.2 (VBUS), U605.5 (VBUS)
WL_PMU_EN: U101.T5 (GPIO_IO14), U901.12 (WL_DSI#/GPIO9)
WL_WAKE_AP: U101.T6 (GPIO_IO15), U901.13 (WL_HOST_WAKE)

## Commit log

2021-04-27 - Initial commit
2021-04-27 - chassis: initial wip C case design
2021-04-27 - pcb: initial mb pcb project
2021-04-27 - doc: update readme - general: add gitignore
2021-04-29 - pcb: working on power supply
2021-04-30 - Upgrade KiCad to latest version - Working on PM circuits - Initial USB Type-C support - Initial support for LCD
2021-05-01 - pcb: switch to imx7 for the prototype
2021-05-01 - readme: reflect updated spec
2021-05-03 - pcb: working on r0p1 sch
2021-05-05 - pcb: r0p1 sch draft
2021-05-06 - pcb: start r0p1 layout
2021-05-07 - pcb: components placed
2021-05-08 - pcb: ddr layout
2021-05-12 - pcb: finishing layout r0p1
2021-05-12 - pcb: r0p1 pdf pre-release
2021-05-13 - pcb: start working on screen board
2021-05-14 - pcb: migrate to latest kicad, r0p1
2021-05-16 - chassis: update design
2021-05-16 - readme: update specs and design
2021-05-16 - chassis: initial step files
2021-05-17 - pcb: add bom for r0p1
2021-05-21 readme: add banner
2021-05-21 pcb: add some 3D models
2021-05-24 chassis: update C/D case design
2021-05-25 fw: initial ec firmware
2021-09-18 sw: add config for uboot and linux
